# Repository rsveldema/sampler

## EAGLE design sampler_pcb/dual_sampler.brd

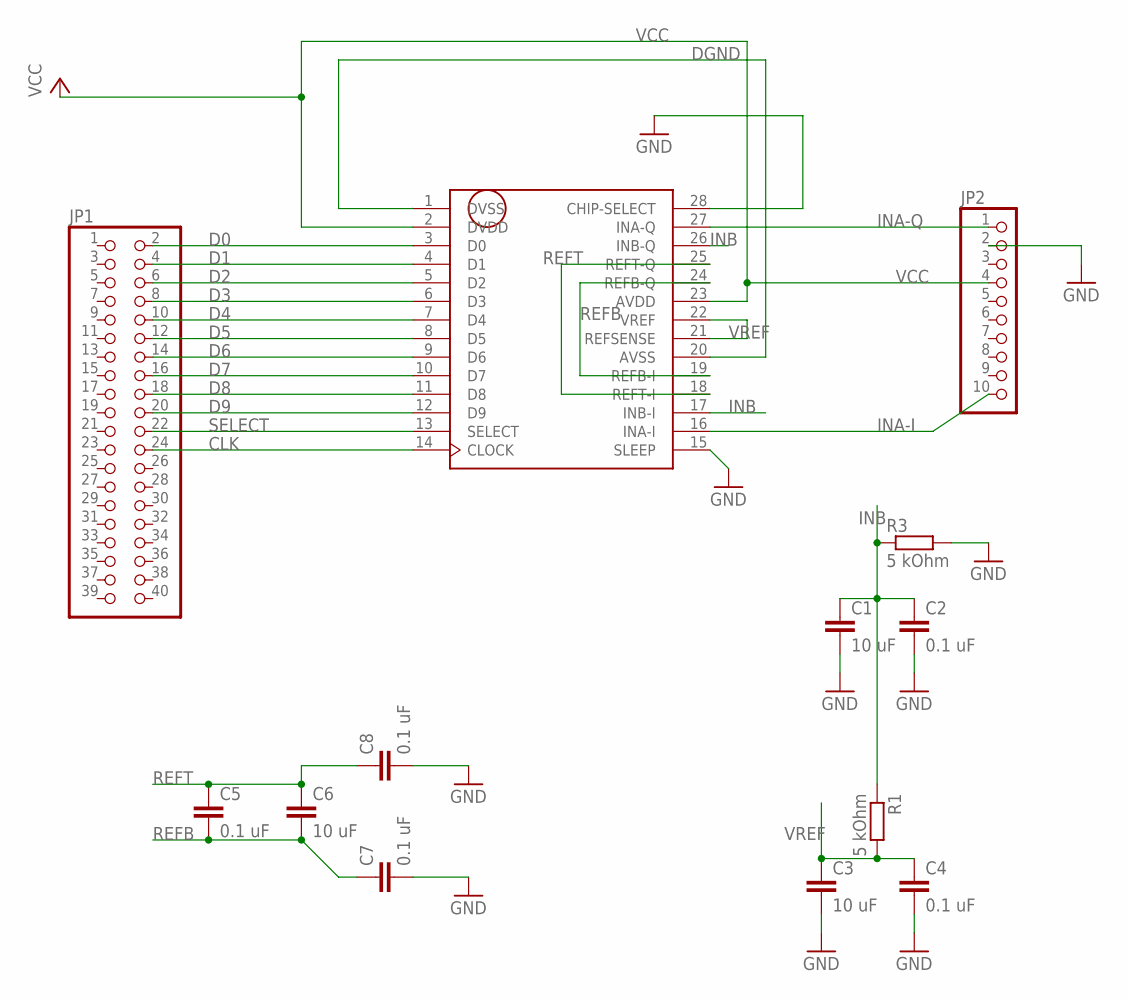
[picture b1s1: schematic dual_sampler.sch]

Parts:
C1, C3, C6: 10 uF; C2.5-3
C2, C4, C5, C7, C8: 0.1 uF; C2.5-3
JP1: PINHD-2X20; 2X20
JP2: PINHD-1X10; 1X10
R1, R3: 5 kOhm; 0204/7
U$1: AD9201ARSZ; SSOP28

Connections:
CLK: JP1.24, U$1.14 (CLOCK)
D0: JP1.2, U$1.3 (D0)
D1: JP1.4, U$1.4 (D1)
D2: JP1.6, U$1.5 (D2)
D3: JP1.8, U$1.6 (D3)
D4: JP1.10, U$1.7 (D4)
D5: JP1.12, U$1.8 (D5)
D6: JP1.14, U$1.9 (D6)
D7: JP1.16, U$1.10 (D7)
D8: JP1.18, U$1.11 (D8)
D9: JP1.20, U$1.12 (D9)
DGND: U$1.1 (DVSS), U$1.20 (AVSS)
GND: C1.2, C2.2, C3.2, C4.2, C7.2, C8.2, JP2.2, R3.2, U$1.15 (SLEEP), U$1.28 (CHIP-SELECT)
INA-I: JP2.10, U$1.16 (INA-I)
INA-Q: JP2.1, U$1.27 (INA-Q)
INB: C1.1, C2.1, R1.1, R3.1, U$1.17 (INB-I), U$1.26 (INB-Q)
REFB: C5.2, C6.2, C7.1, U$1.19 (REFB-I), U$1.24 (REFB-Q)
REFT: C5.1, C6.1, C8.1, U$1.18 (REFT-I), U$1.25 (REFT-Q)
SELECT: JP1.22, U$1.13 (SELECT)
VCC: JP2.4, U$1.2 (DVDD), U$1.23 (AVDD)
VREF: C3.1, C4.1, R1.2, U$1.21 (REFSENSE), U$1.22 (VREF)

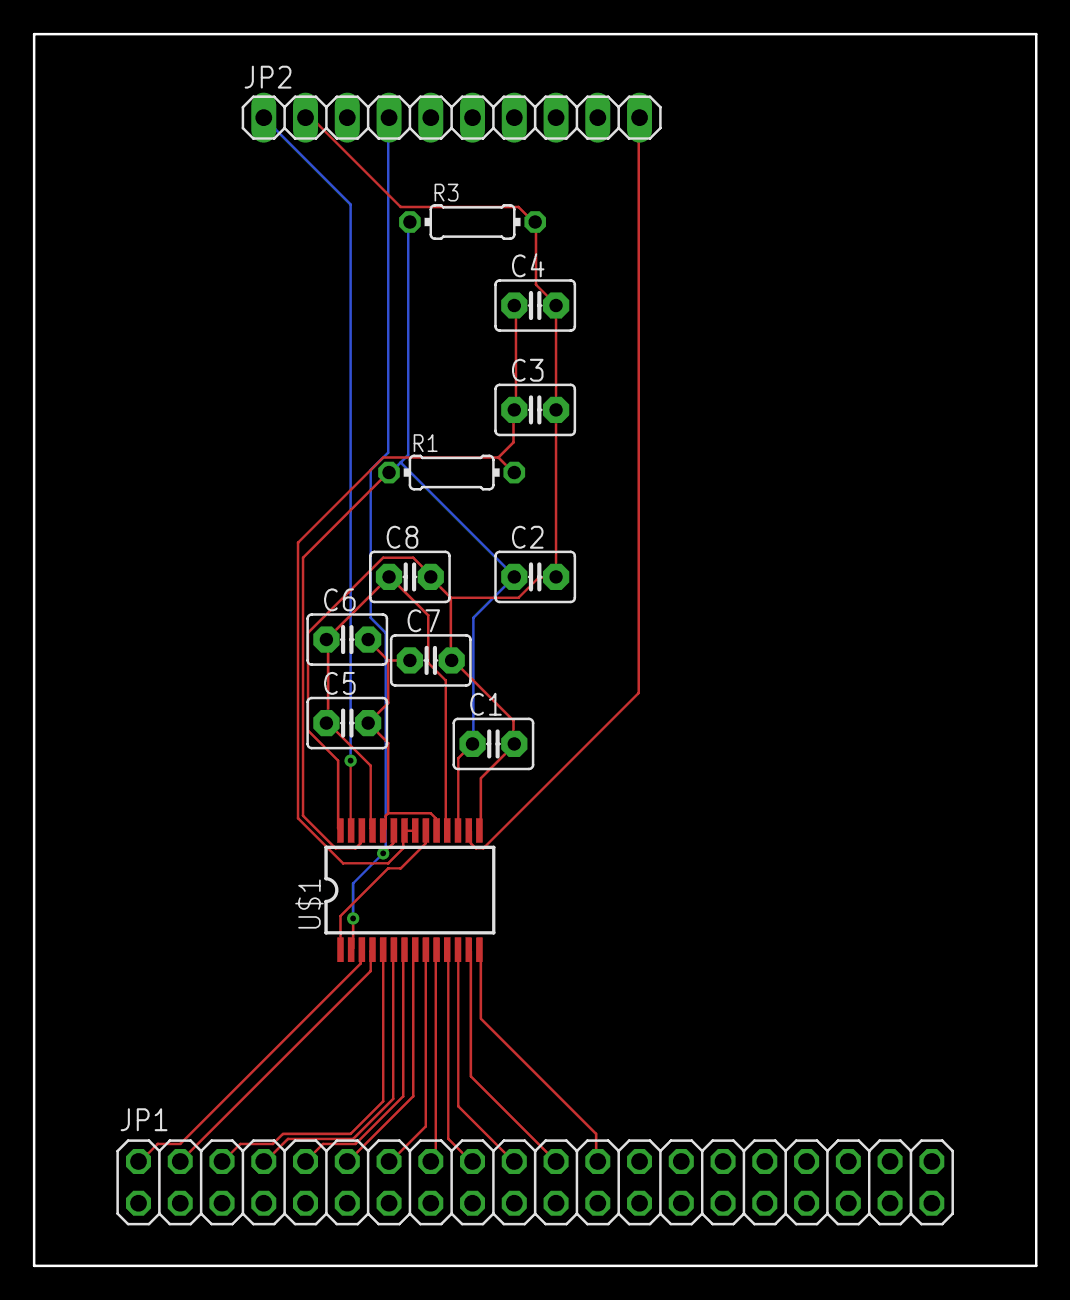
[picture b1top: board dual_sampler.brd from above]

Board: 2 copper layers, 61.0 x 74.9 mm, 13 parts (0 on the bottom side), 21 nets.

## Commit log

2017-06-15 - nios II with jtag-uart, local memory in qsys - niosII firmware with bsp with hello world
2017-06-25 LEDs work
2017-06-25 updated with sdram controller...
2017-06-25 sdram test works ok.
2017-06-25 sdram works.
2017-06-25 missing files `
2017-08-06 - datasheet added - start at PCB description with ki-cad
2017-08-06 pcb bugfix.
2017-08-06 picked footprints
2017-08-10 pcb update
2017-08-12 autoplaced
2017-09-26 next attempt with eagle
2017-10-22 updated schematic, 1st try at board
2017-11-01 updated autocad's Eagle files, latest is schematic with PCB with GND-added.
